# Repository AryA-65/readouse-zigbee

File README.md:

# readouse-zigbee
Simple and cheap zigbee plant moisture sensor

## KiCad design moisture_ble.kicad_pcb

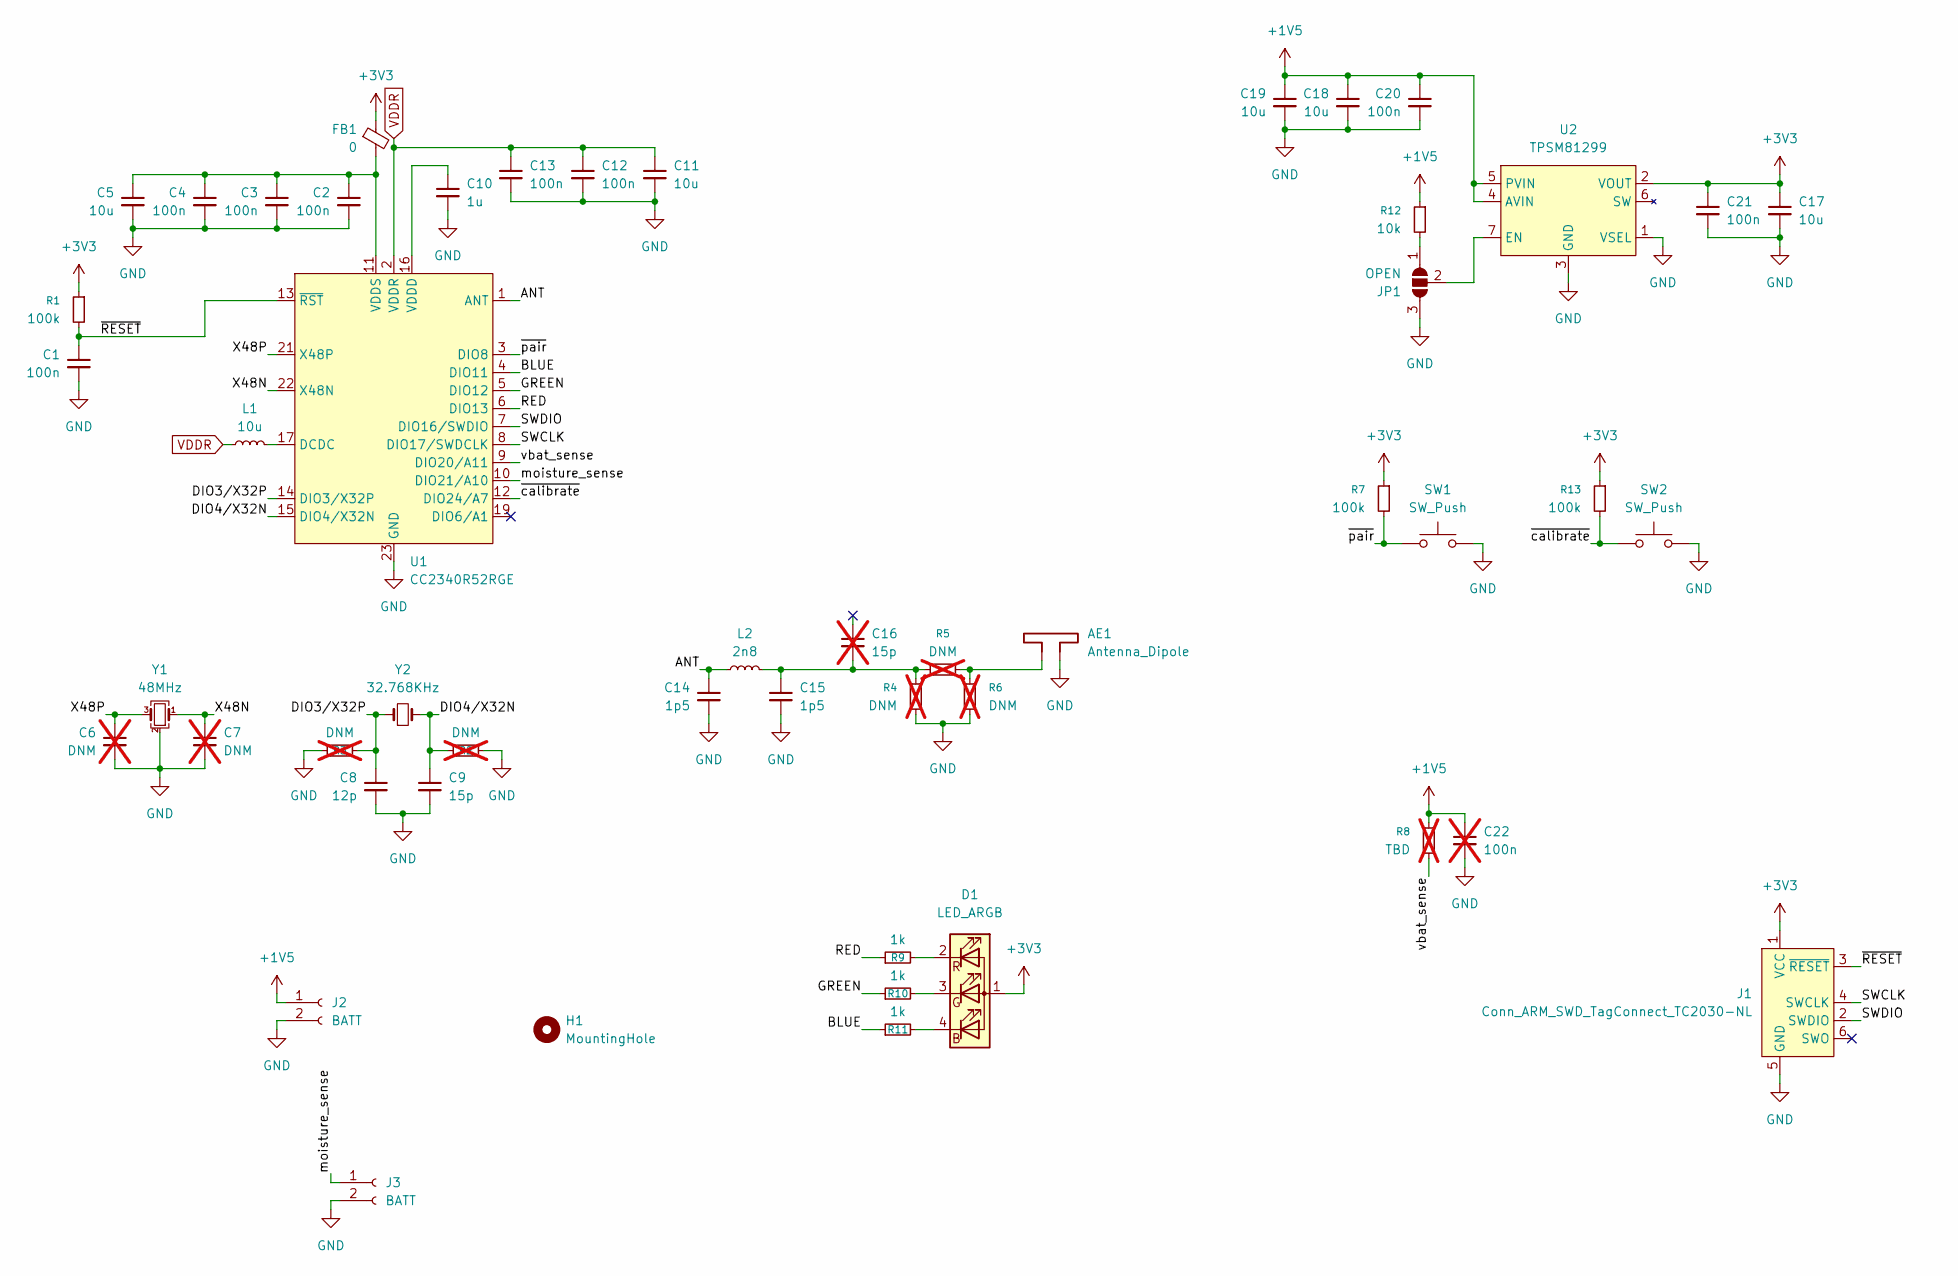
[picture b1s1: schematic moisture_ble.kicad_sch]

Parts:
AE1: Antenna_Dipole; Texas_SWRA117D_2.4GHz_Right
C1, C2, C3, C4, C12, C13, C20, C21: 100n; C_0402_1005Metric; Part Num. GRM155C71H104JE19D
C5, C11, C17, C18, C19: 10u; C_0603_1608Metric; Part Num. GRM188Z71A106KA73D
C6, C7: DNM; C_0402_1005Metric; not fitted
C8: 12p; C_0402_1005Metric
C9: 15p; C_0402_1005Metric
C10: 1u; C_0402_1005Metric; Part Num. GRM155Z71A105KE01D
C14, C15: 1p5; C_0402_1005Metric; Part Num. CL05C1R5BB5NNNC
C16: 15p; C_0402_1005Metric; not fitted
C22: 100n; C_0402_1005Metric; Part Num. GRM155C71H104JE19D; not fitted
D1: LED_ARGB; 150044M155260
FB1: 0; R_0603_1608Metric; Part Num. RK73Z1JTTD
H1: MountingHole; MountingHole_2.2mm_M2
J1: Conn_ARM_SWD_TagConnect_TC2030-NL; Tag-Connect_TC2030-IDC-NL_2x03_P1.27mm_Vertical
J2, J3: BATT; JST_PH_S2B-PH-K_1x02_P2.00mm_Horizontal
JP1: OPEN; SolderJumper-3_P1.3mm_Open_RoundedPad1.0x1.5mm
L1: 10u; L_0603_1608Metric; Part Num. LQM18DN100M70L
L2: 2n8; L_0402_1005Metric; Part Num. LQG15WZ2N8B02D
R1, R7, R13: 100k; R_0402_1005Metric; Part Num. ERJ-2GEJ104X
R2, R3, R4, R5, R6: DNM; R_0402_1005Metric; not fitted
R8: TBD; R_0402_1005Metric; Part Num. ERJ-2GEJ104X; not fitted
R9, R10, R11: 1k; R_0402_1005Metric
R12: 10k; R_0402_1005Metric
SW1, SW2: SW_Push; SW_SPST_EVQP2_ShortPushTravel_H2.1mm
U1: CC2340R52RGE; QFN-24-1EP_4x4mm_P0.5mm_EP2.15x2.15mm
U2: TPSM81299; VCM0007A-MFG
Y1: 48MHz; Crystal_SMD_2016-4Pin_2.0x1.6mm; Part Num. CX3225FB48000C0FZZH1
Y2: 32.768KHz; Crystal_SMD_2012-2Pin_2.0x1.2mm; Part Num. Q 0,032768-JTX210-7-20-T1-HMR-70K-LF

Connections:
+1V5: C18.1, C19.1, C20.1, C22.1, J2.1, R8.1, R12.1, U2.4 (AVIN), U2.5 (PVIN)
+3V3: C17.1, C21.1, D1.1 (A), FB1.1, J1.1 (VCC), R1.1, R7.1, R13.1, U2.2 (VOUT)
/ANT: C14.1, L2.1, U1.1 (ANT)
/BLUE: R11.1, U1.4 (DIO11)
/DIO3/X32P: C8.1, R3.2, U1.14 (DIO3/X32P), Y2.1
/DIO4/X32N: C9.1, R2.1, U1.15 (DIO4/X32N), Y2.2
/GREEN: R10.1, U1.5 (DIO12)
/RED: R9.1, U1.6 (DIO13)
/SWCLK: J1.4 (SWCLK), U1.8 (DIO17/SWDCLK)
/SWDIO: J1.2 (SWDIO), U1.7 (DIO16/SWDIO)
/X48N: C7.1, U1.22 (X48N), Y1.1
/X48P: C6.1, U1.21 (X48P), Y1.3
/moisture_sense: J3.1, U1.10 (DIO21/A10)
/vbat_sense: R8.2, U1.9 (DIO20/A11)
/~RESET: C1.1, J1.3 (~RESET), R1.2, U1.13 (~RST)
/~calibrate: R13.2, SW2.1, U1.12 (DIO24/A7)
/~pair: R7.2, SW1.1, U1.3 (DIO8)
GND: AE1.2, C1.2, C2.2, C3.2, C4.2, C5.2, C6.2, C7.2, C8.2, C9.2, C10.2, C11.2, C12.2, C13.2, C14.2, C15.2, C17.2, C18.2, C19.2, C20.2, C21.2, C22.2, J1.5 (GND), J2.2, J3.2, JP1.3 (B), R2.2, R3.1, R4.1, R6.2, SW1.2, SW2.2, U1.23 (GND), U1.25 (EPAD), U2.1 (VSEL), U2.3 (GND), Y1.2 (G), Y1.4 (G)
unnamed: AE1.1, R5.2, R6.1
unnamed: C2.1, C3.1, C4.1, C5.1, FB1.2, U1.11 (VDDS), U1.18 (VDDS), U1.24 (VDDS)
unnamed: C15.1, C16.2, L2.2, R4.2, R5.1
unnamed: D1.4 (BK), R11.2
unnamed: D1.3 (GK), R10.2
unnamed: D1.2 (RK), R9.2
unnamed: JP1.1 (A), R12.2
unnamed: JP1.2 (C), U2.7 (EN)
unnamed: L1.2, U1.17 (DCDC)
unnamed: C10.1, U1.16 (VDDD)
VDDR: C11.1, C12.1, C13.1, L1.1, U1.2 (VDDR), U1.20 (VDDR)

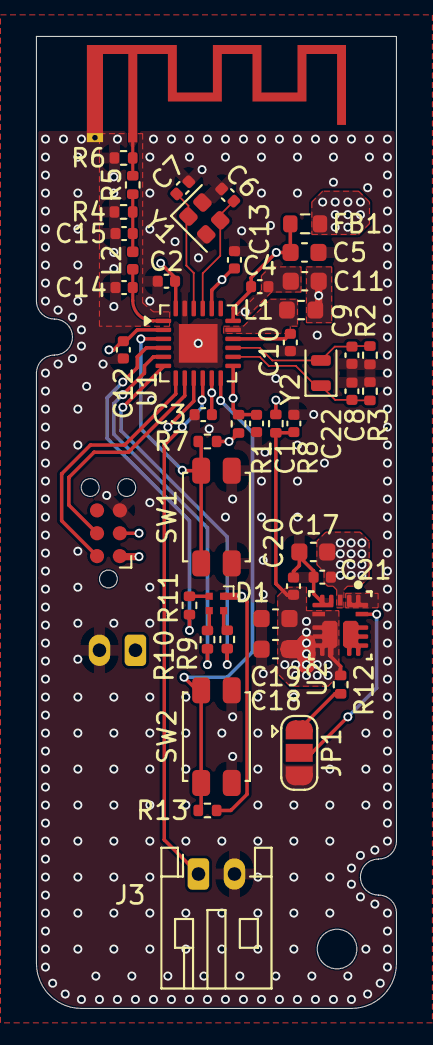
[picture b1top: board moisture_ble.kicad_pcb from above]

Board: 4 copper layers, 20.0 x 54.0 mm, 50 parts (1 on the bottom side), 29 nets.
